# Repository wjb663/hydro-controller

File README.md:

# 26-Computer-Vision-based-hydroponic-control-system

Navigate to "features" branch to get the latest version of the files capable of being ran.

ModusToolbox installation link: https://www.infineon.com/cms/en/design-support/tools/sdk/modustoolbox-software/

Select CY8CPROTO-062-4343W when the IDE has loaded and it will download the relevant drivers. Download WiFi-MQTT_Client_Code example program and replace the code in the files with the code from the features branch. Then run the program and it'll flash to the board.

For the camera:
Two ESP-32s are needed to run the current version of the working code - one for the camera capture, one for the sensor code. The hardware files in our Google drive contain the KICAD files for the camera PCB. There are two version of the camera board - one using an ESP-32 breakout board, the second using a soldered on ESP 32. Both PCB designs contain the pinouts for how the DHT11 sensor, the ambient light sensor, and the Arducam should be connected to each camera board/ESP 32. Connect the DHT11 and ambient light sensor to one ESP32, the ArduCAM to the second.

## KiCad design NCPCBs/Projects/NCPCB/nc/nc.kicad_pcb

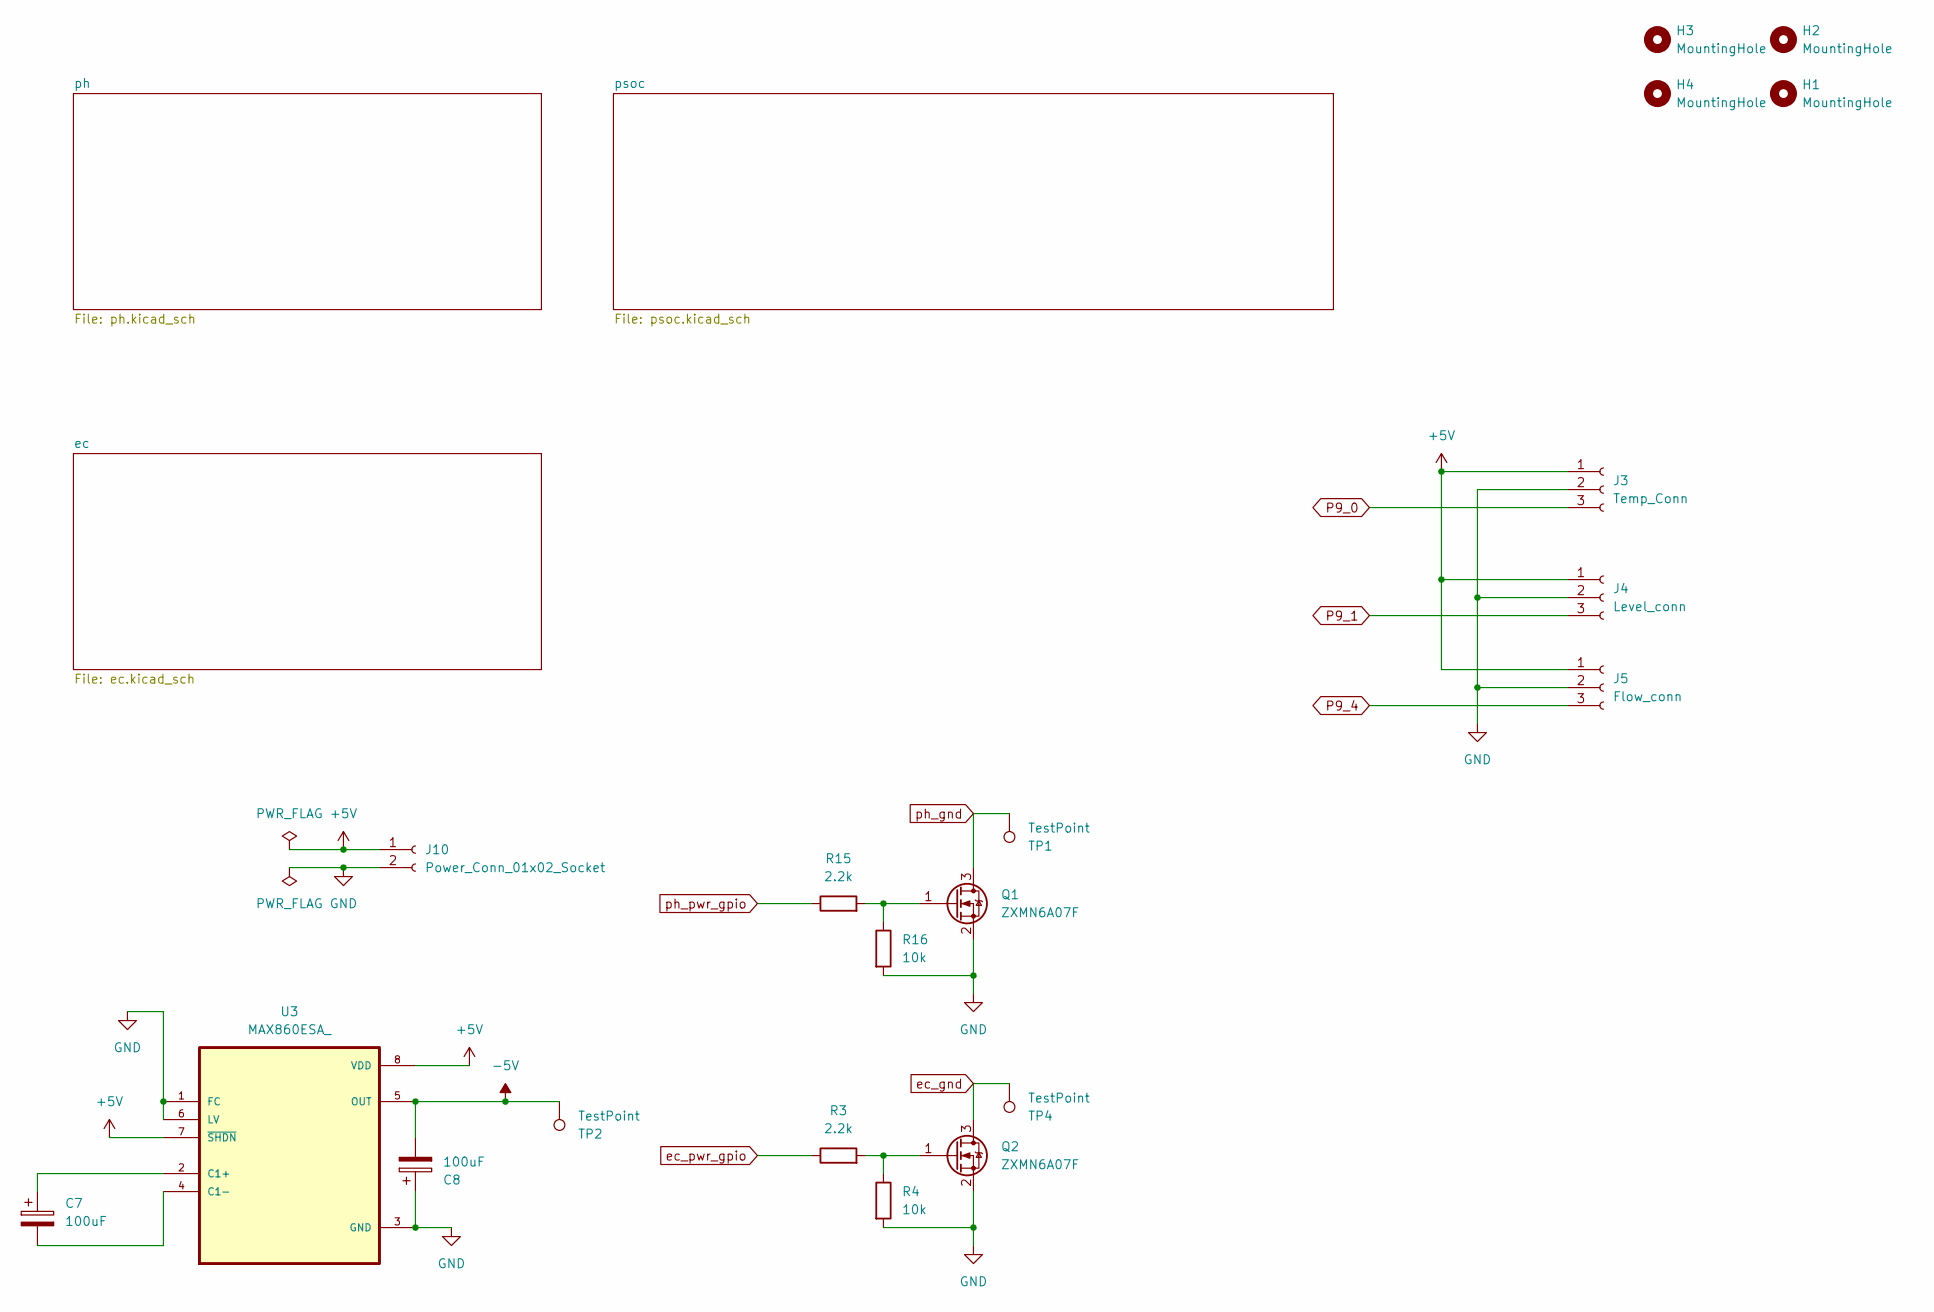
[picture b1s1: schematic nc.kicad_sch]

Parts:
C7, C8: 100uF; CP_EIA-3216-10_Kemet-I_Pad1.58x1.35mm_HandSolder
H1, H2, H3, H4: MountingHole; MountingHole_3.2mm_M3
J3: Temp_Conn; JST_EH_B3B-EH-A_1x03_P2.50mm_Vertical
J4: Level_conn; JST_EH_B3B-EH-A_1x03_P2.50mm_Vertical
J5: Flow_conn; JST_EH_B3B-EH-A_1x03_P2.50mm_Vertical
J10: Power_Conn_01x02_Socket; JST_PH_B2B-PH-K_1x02_P2.00mm_Vertical
Q1, Q2: ZXMN6A07F; SOT-23
R3, R15: 2.2k; R_0805_2012Metric_Pad1.20x1.40mm_HandSolder
R4, R16: 10k; R_0805_2012Metric_Pad1.20x1.40mm_HandSolder
TP1, TP2, TP4: TestPoint; TestPoint_Pad_1.0x1.0mm
U3: MAX860ESA_; SOIC127P600X175-8N

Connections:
+5V: J3.1, J4.1, J5.1, J10.1, U3.7 (~SHDN), U3.8 (VDD); also elsewhere on the board
-5V: C8.2, TP2.1, U3.5 (OUT); also elsewhere on the board
GND: C8.1, J3.2, J4.2, J5.2, J10.2, Q1.2 (S), Q2.2 (S), R4.2, R16.2, U3.1 (FC), U3.3 (GND), U3.6 (LV); also elsewhere on the board
unnamed: Q1.1 (G), R15.2, R16.1
unnamed: Q2.1 (G), R3.2, R4.1
unnamed: C7.1, U3.2 (C1+)
unnamed: C7.2, U3.4 (C1-)
P9_0: J3.3; also elsewhere on the board
P9_1: J4.3; also elsewhere on the board
P9_4: J5.3; also elsewhere on the board
P11_4: R15.1; also elsewhere on the board
P12_3: R3.1; also elsewhere on the board
ec_gnd: Q2.3 (D), TP4.1; also elsewhere on the board
ph_gnd: Q1.3 (D), TP1.1; also elsewhere on the board

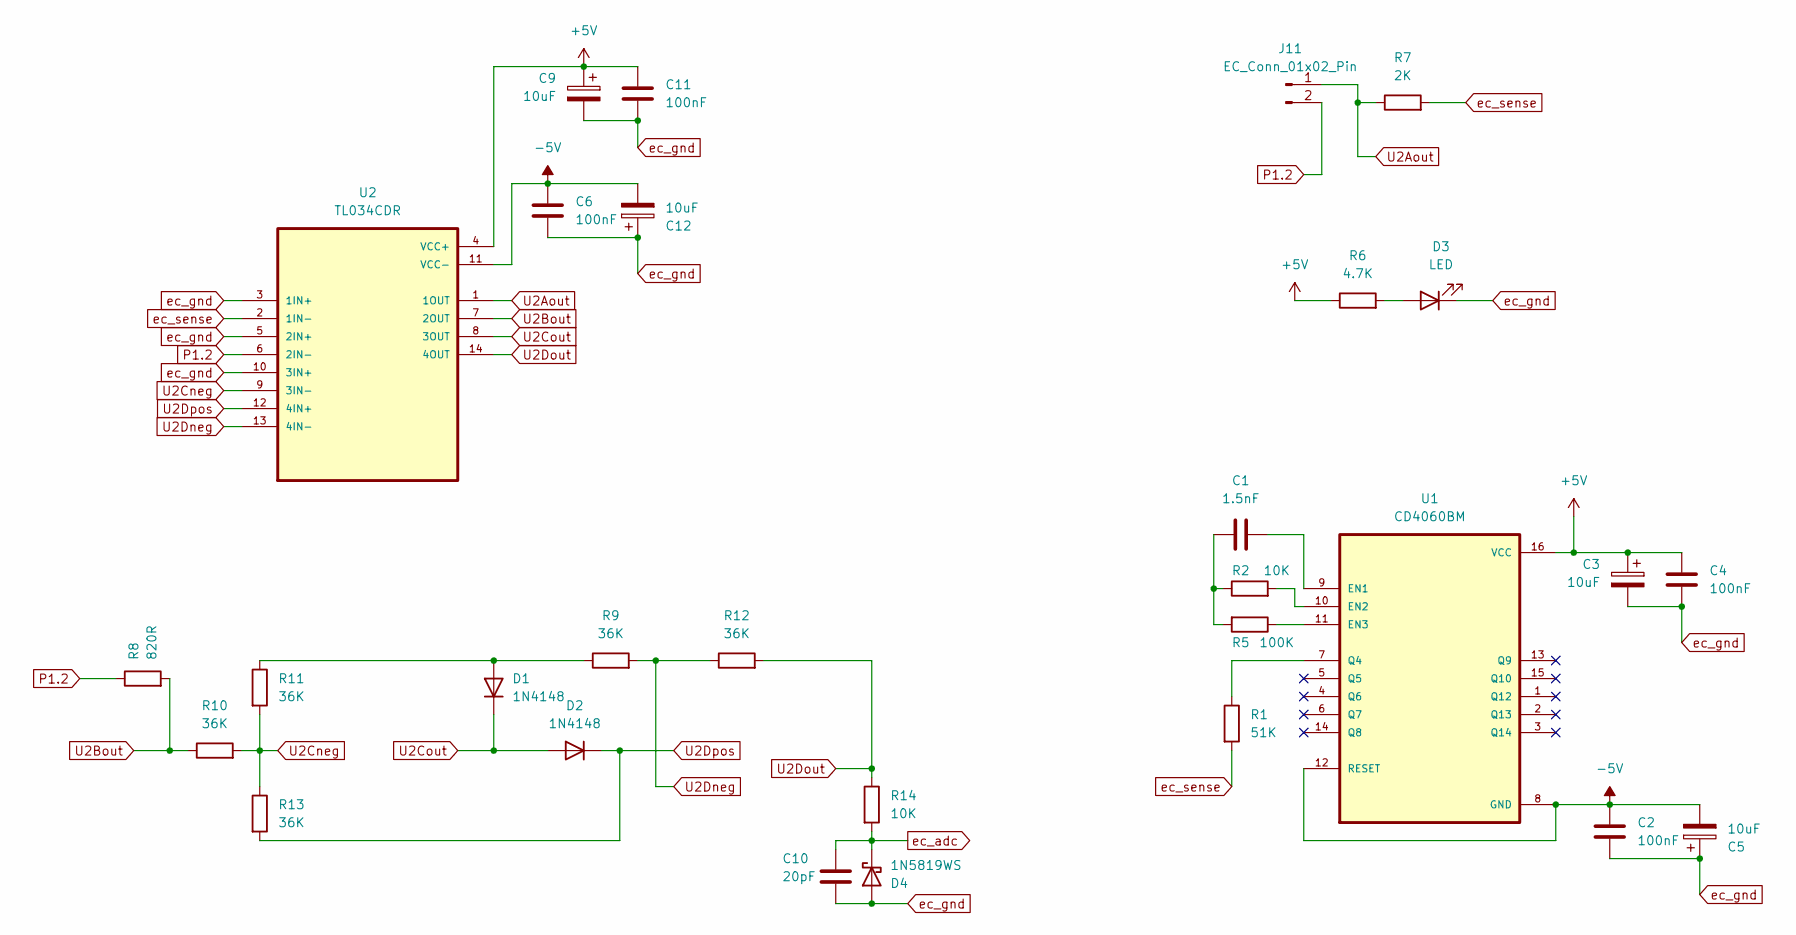
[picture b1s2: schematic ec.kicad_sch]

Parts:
C1: 1.5nF; C_0805_2012Metric_Pad1.18x1.45mm_HandSolder
C2, C4, C6, C11: 100nF; C_0805_2012Metric_Pad1.18x1.45mm_HandSolder
C3, C5, C9, C12: 10uF; CP_EIA-3216-10_Kemet-I_Pad1.58x1.35mm_HandSolder
C10: 20pF; C_0805_2012Metric_Pad1.18x1.45mm_HandSolder
D1, D2: 1N4148; D_DO-35_SOD27_P7.62mm_Horizontal
D3: LED; LED_0805_2012Metric_Pad1.15x1.40mm_HandSolder
D4: 1N5819WS; D_SOD-323
J11: EC_Conn_01x02_Pin; JST_EH_B2B-EH-A_1x02_P2.50mm_Vertical
R1: 51K; R_0805_2012Metric_Pad1.20x1.40mm_HandSolder
R2, R14: 10K; R_0805_2012Metric_Pad1.20x1.40mm_HandSolder
R5: 100K; R_0805_2012Metric_Pad1.20x1.40mm_HandSolder
R6: 4.7K; R_0805_2012Metric_Pad1.20x1.40mm_HandSolder
R7: 2K; R_0805_2012Metric_Pad1.20x1.40mm_HandSolder
R8: 820R; R_0805_2012Metric_Pad1.20x1.40mm_HandSolder
R9, R10, R11, R12, R13: 36K; R_0805_2012Metric_Pad1.20x1.40mm_HandSolder
U1: CD4060BM; SOIC127P600X175-16N
U2: TL034CDR; SOIC127P600X175-14N

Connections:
+5V: C3.1, C4.1, C9.1, C11.1, R6.1, U1.16 (VCC), U2.4 (VCC+); also elsewhere on the board
-5V: C2.1, C5.2, C6.1, C12.2, U1.8 (GND), U1.12 (RESET), U2.11 (VCC-); also elsewhere on the board
unnamed: C1.1, R2.1, R5.2
unnamed: D1.2 (A), R9.1, R11.1
unnamed: D3.2 (A), R6.2
unnamed: C1.2, U1.9 (EN1)
unnamed: R2.2, U1.10 (EN2)
unnamed: R5.1, U1.11 (EN3)
unnamed: R1.1, U1.7 (Q4)
P1.2: J11.2, R8.1, U2.6 (2IN-)
P10_3: C10.1, D4.1 (K), R14.2; also elsewhere on the board
U2Aout: J11.1, R7.1, U2.1 (1OUT)
U2Bout: R8.2, R10.1, U2.7 (2OUT)
U2Cneg: R10.2, R11.2, R13.1, U2.9 (3IN-)
U2Cout: D1.1 (K), D2.2 (A), U2.8 (3OUT)
U2Dneg: R9.2, R12.1, U2.13 (4IN-)
U2Dout: R12.2, R14.1, U2.14 (4OUT)
U2Dpos: D2.1 (K), R13.2, U2.12 (4IN+)
ec_gnd: C2.2, C3.2, C4.2, C5.1, C6.2, C9.2, C10.2, C11.2, C12.1, D3.1 (K), D4.2 (A), U2.3 (1IN+), U2.5 (2IN+), U2.10 (3IN+); also elsewhere on the board
ec_sense: R1.2, R7.2, U2.2 (1IN-)

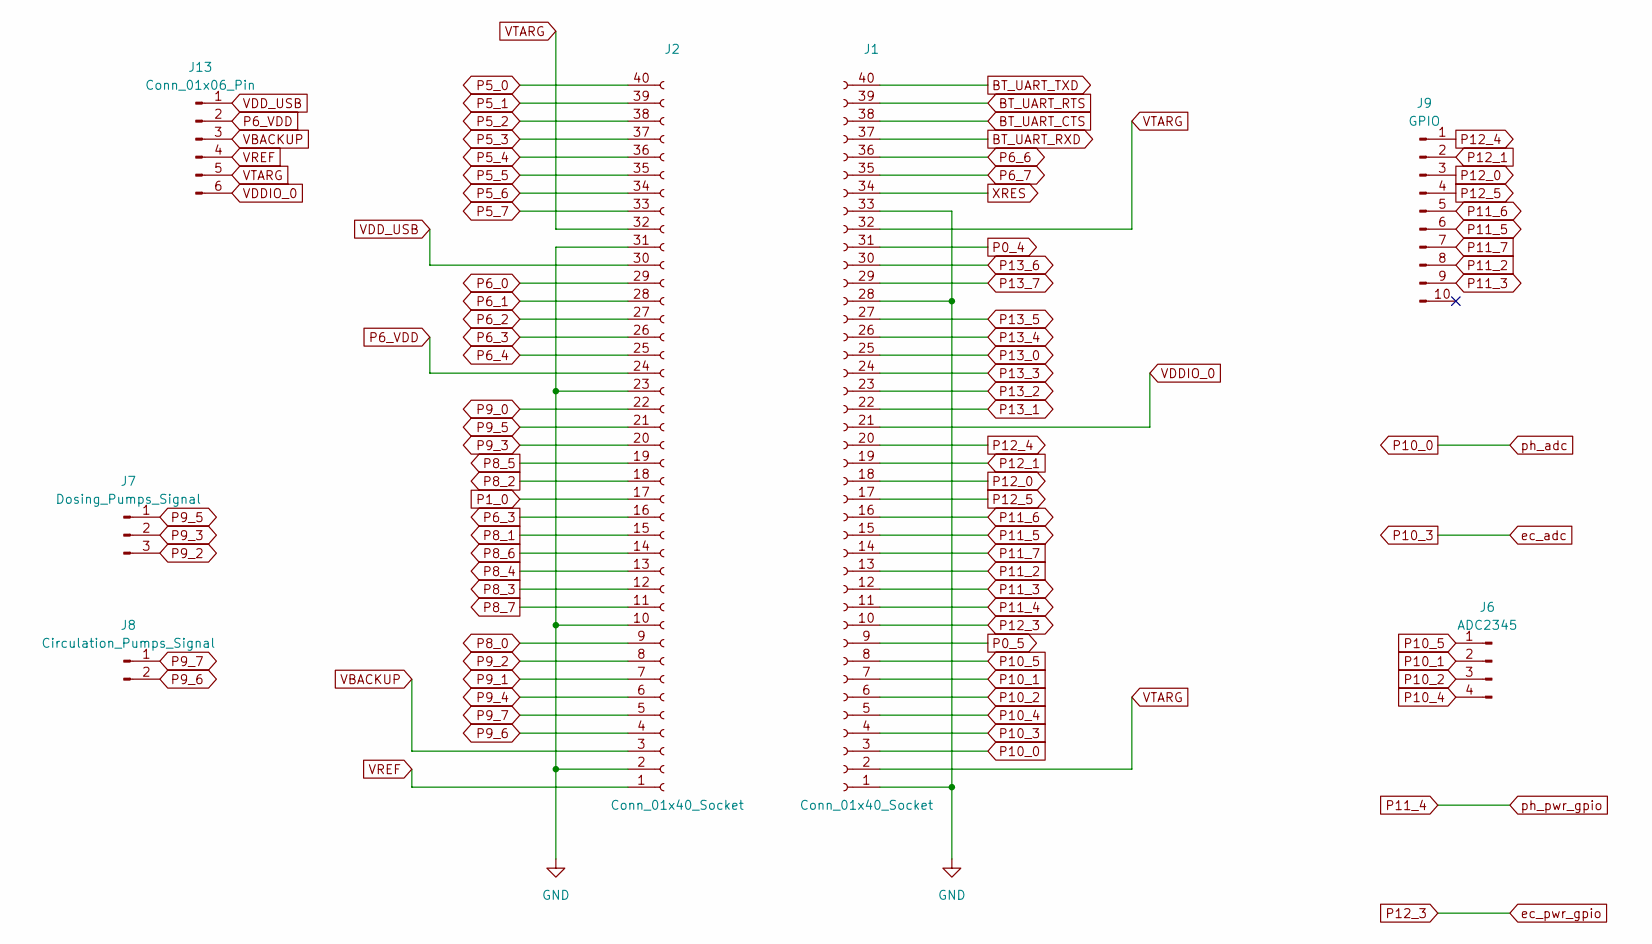
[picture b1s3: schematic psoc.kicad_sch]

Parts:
J1, J2: Conn_01x40_Socket; PinSocket_1x40_P2.00mm_Vertical
J6: ADC2345; PinHeader_1x04_P2.00mm_Vertical
J7: Dosing_Pumps_Signal; JST_EH_B3B-EH-A_1x03_P2.50mm_Vertical
J8: Circulation_Pumps_Signal; JST_EH_B2B-EH-A_1x02_P2.50mm_Vertical
J9: GPIO; PinHeader_1x10_P2.00mm_Vertical
J13: Conn_01x06_Pin; PinHeader_1x06_P2.00mm_Vertical

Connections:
BT_UART_CTS: J1.38
BT_UART_RTS: J1.39
BT_UART_RXD: J1.37
BT_UART_TXD: J1.40
GND: J1.1, J1.28, J1.33, J2.2, J2.10, J2.23, J2.31; also elsewhere on the board
P0_4: J1.31
P0_5: J1.9
P1_0: J2.17
P5_0: J2.40
P5_1: J2.39
P5_2: J2.38
P5_3: J2.37
P5_4: J2.36
P5_5: J2.35
P5_6: J2.34
P5_7: J2.33
P6_0: J2.29
P6_1: J2.28
P6_2: J2.27
P6_3: J2.16, J2.26
P6_4: J2.25
P6_6: J1.36
P6_7: J1.35
P6_VDD: J2.24, J13.2
P8_0: J2.9
P8_1: J2.15
P8_2: J2.18
P8_3: J2.12
P8_4: J2.13
P8_5: J2.19
P8_6: J2.14
P8_7: J2.11
P9_0: J2.22; also elsewhere on the board
P9_1: J2.7; also elsewhere on the board
P9_2: J2.8, J7.3
P9_3: J2.20, J7.2
P9_4: J2.6; also elsewhere on the board
P9_5: J2.21, J7.1
P9_6: J2.4, J8.2
P9_7: J2.5, J8.1
P10_0: J1.3; also elsewhere on the board
P10_1: J1.7, J6.2
P10_2: J1.6, J6.3
P10_3: J1.4; also elsewhere on the board
P10_4: J1.5, J6.4
P10_5: J1.8, J6.1
P11_2: J1.13, J9.8
P11_3: J1.12, J9.9
P11_4: J1.11; also elsewhere on the board
P11_5: J1.15, J9.6
P11_6: J1.16, J9.5
P11_7: J1.14, J9.7
P12_0: J1.18, J9.3
P12_1: J1.19, J9.2
P12_3: J1.10; also elsewhere on the board
P12_4: J1.20, J9.1
P12_5: J1.17, J9.4
P13_0: J1.25
P13_1: J1.22
P13_2: J1.23
P13_3: J1.24
P13_4: J1.26
P13_5: J1.27
P13_6: J1.30
P13_7: J1.29
VBACKUP: J2.3, J13.3
VDDIO_0: J1.21, J13.6
VDD_USB: J2.30, J13.1
VREF: J2.1, J13.4
VTARG: J1.2, J1.32, J2.32, J13.5
XRES: J1.34

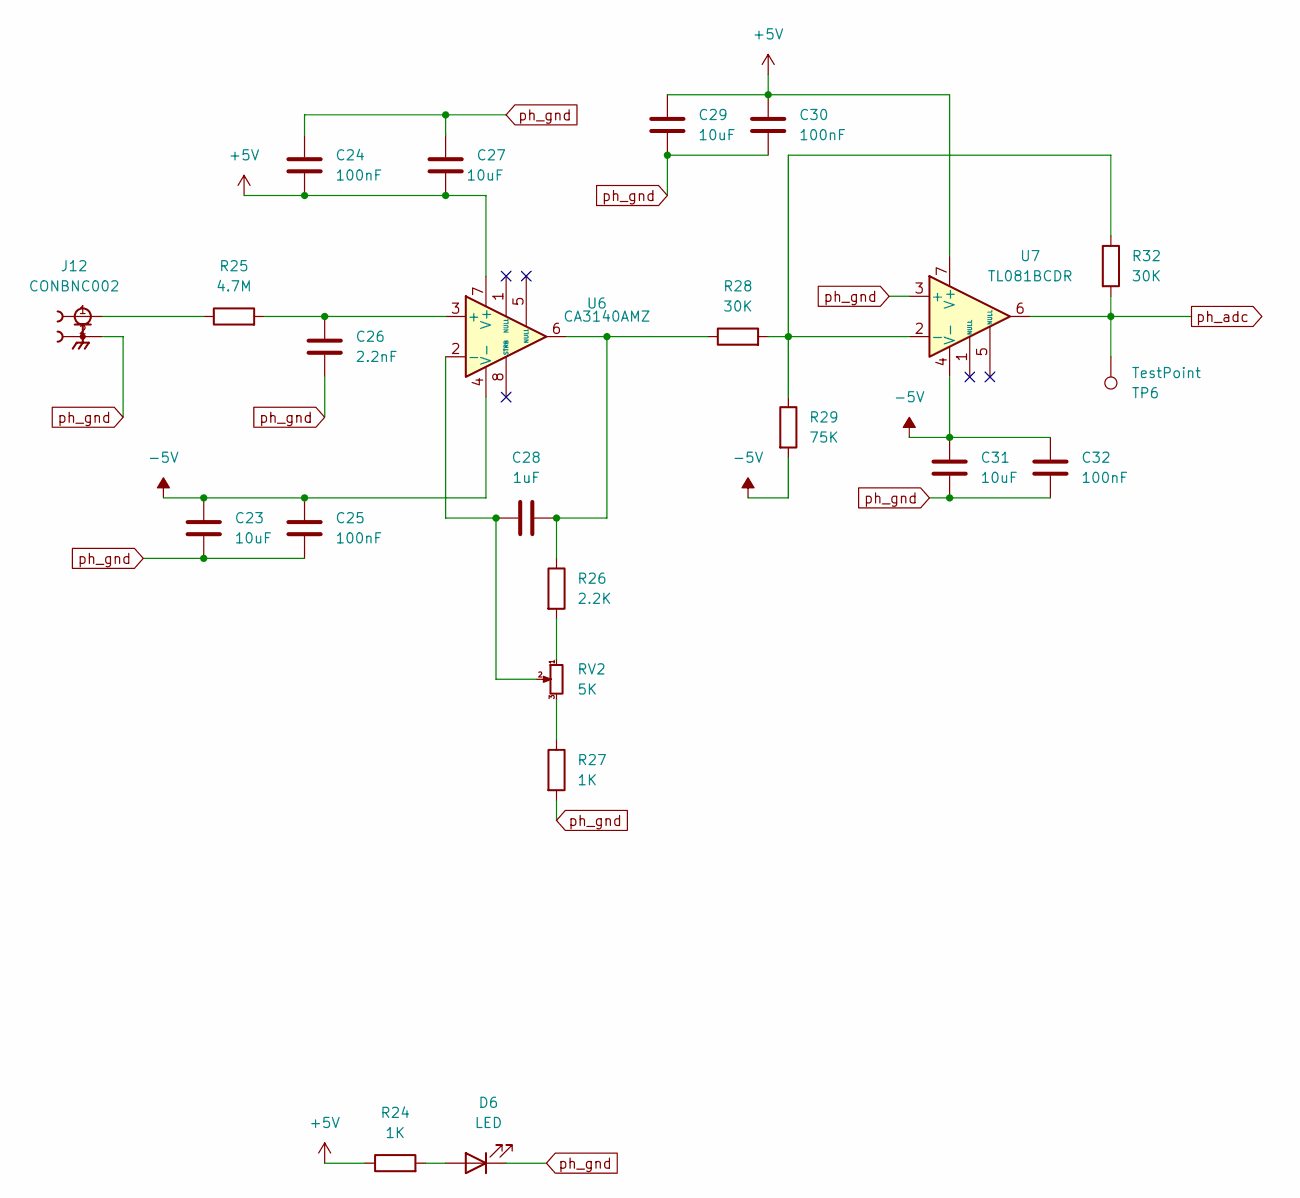
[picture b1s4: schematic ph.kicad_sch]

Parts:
C23, C27, C29, C31: 10uF; C_0805_2012Metric_Pad1.18x1.45mm_HandSolder
C24, C25, C30, C32: 100nF; C_0805_2012Metric_Pad1.18x1.45mm_HandSolder
C26: 2.2nF; C_0805_2012Metric_Pad1.18x1.45mm_HandSolder
C28: 1uF; C_0805_2012Metric_Pad1.18x1.45mm_HandSolder
D6: LED; LED_0805_2012Metric_Pad1.15x1.40mm_HandSolder
J12: CONBNC002; LINX_CONBNC002
R24, R27: 1K; R_0805_2012Metric_Pad1.20x1.40mm_HandSolder
R25: 4.7M; R_0805_2012Metric_Pad1.20x1.40mm_HandSolder
R26: 2.2K; R_0805_2012Metric_Pad1.20x1.40mm_HandSolder
R28, R32: 30K; R_0805_2012Metric_Pad1.20x1.40mm_HandSolder
R29: 75K; R_0805_2012Metric_Pad1.20x1.40mm_HandSolder
RV2: 5K; Potentiometer_Bourns_3266W_Vertical
TP6: TestPoint; TestPoint_Pad_1.0x1.0mm
U6: CA3140AMZ; SOIC-8_3.9x4.9mm_P1.27mm
U7: TL081BCDR; SOIC-8_3.9x4.9mm_P1.27mm

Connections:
+5V: C24.2, C27.2, C29.1, C30.1, R24.1, U6.7 (V+), U7.7 (V+); also elsewhere on the board
-5V: C23.1, C25.1, C31.1, C32.1, R29.2, U6.4 (V-), U7.4 (V-); also elsewhere on the board
unnamed: C28.2, R26.1, R28.1, U6.6
unnamed: D6.2 (A), R24.2
unnamed: J12.1, R25.1
unnamed: R26.2, RV2.1
unnamed: R27.1, RV2.3
unnamed: C26.1, R25.2, U6.3 (+)
unnamed: C28.1, RV2.2, U6.2 (-)
unnamed: R28.2, R29.1, R32.1, U7.2 (-)
P10_0: R32.2, TP6.1, U7.6; also elsewhere on the board
ph_gnd: C23.2, C24.1, C25.2, C26.2, C27.1, C29.2, C30.2, C31.2, C32.2, D6.1 (K), J12.2, R27.2, U7.3 (+); also elsewhere on the board

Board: 2 copper layers, 79 parts (0 on the bottom side), 65 nets, no tracks yet.

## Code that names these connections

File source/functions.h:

#include "cybsp.h"
#include "cyhal.h"


#ifndef SOURCE_SENSOR_FUNCTIONS_H_
#define SOURCE_SENSOR_FUNCTIONS_H_

#define VPLUS_CHANNEL_0  (P10_0)
#define VPLUS_CHANNEL_1  (P10_3)
#define VREF_CHANNEL_1   (P10_5)

/* Number of scans every time ADC read is initiated */
#define NUM_SCAN                    (1)

/* Conversion factor */
#define MICRO_TO_MILLI_CONV_RATIO        (1000u)

/* Acquistion time in nanosecond */
#define ACQUISITION_TIME_NS              (1000u)

/* ADC Scan delay in millisecond */
#define ADC_SCAN_DELAY_MS                (200u)
#define NUM_READINGS					 (10)

/* Number of scans every time ADC read is initiated */
#define NUM_SCAN                         (1)

//Pin Macros
#define PH_FET                          (P11_4)
#define EC_FET                          (P12_3)

#define PUMP_ONE                        (P9_5)
#define PUMP_TWO                        (P9_3)
#define PUMP_THREE                      (P9_2)
#define PUMP_FOUR                       (P9_7)
#define PUMP_FIVE                       (P9_6)

void gpio_init();

void adc_multi_channel_init(void);
cy_rslt_t result_return(void);
int32_t channel0_return(void);
int32_t channel1_return(void);

#endif /* SOURCE_SENSOR_FUNCTIONS_H_ */

/*******************************************************************************
* Function Prototypes
*******************************************************************************/
void timer_init(void);


/* Single channel initialization function*/
void adc_single_channel_init(void);

/* Function to read input voltage from channel 0 */
void adc_single_channel_process(void);

//Temp Sensor Functions
void initialize_wire(void);
void wire_process(void *pvParameters);
void write_wire_byte(uint8_t data);
void read_wire(void);
void print_wire(void);

//Pumps
// void pump_task(void *pvParameters);

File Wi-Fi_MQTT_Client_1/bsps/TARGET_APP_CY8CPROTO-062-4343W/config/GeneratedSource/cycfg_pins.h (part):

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    #define CYBSP_USER_BTN1 CYBSP_SW2
    #define CYBSP_USER_BTN CYBSP_SW2
    #define CYBSP_WIFI_HOST_WAKE CYBSP_SW2
    #define CYBSP_PDM_CLK (P10_4)
    #define CYBSP_PDM_DATA (P10_5)
    #define CYBSP_QSPI_SS (P11_2)
    #define CYBSP_QSPI_D3 (P11_3)
    #define CYBSP_QSPI_D2 (P11_4)
    #define CYBSP_QSPI_D1 (P11_5)
    #define CYBSP_QSPI_D0 (P11_6)
    #define CYBSP_QSPI_SCK (P11_7)
    #define CYBSP_SDHC_CMD (P12_4)
    #define CYBSP_SDHC_CLK (P12_5)
    #define CYBSP_SDHC_IO0 (P13_0)
    #define CYBSP_SDHC_IO1 (P13_1)
    #define CYBSP_SDHC_IO2 (P13_2)
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
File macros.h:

//Macros for program
#include "cyhal.h"


typedef enum transaction{
    RESET,
    PRESENSE,
    SKIP_ROM,
    CONVERT_T,
    POLL,
    SCRATCH,
    PARSE,
    DONE,
    ERROR,
} transaction_t;



/*******************************************************************************
* Macros
*******************************************************************************/
/* LED blink timer clock value in Hz  */
#define LED_BLINK_TIMER_CLOCK_HZ          (10000)

/* LED blink timer period value */
#define LED_BLINK_TIMER_PERIOD            (9999)

#define PUMP_TIMER_CLOCK_HZ               (10000)
#define PUMP_TIMER_PERIOD                 (9999)

#define WIRE_TIMER_CLOCK_HZ               (100000)
#define WIRE_TIMER_PERIOD                 (50)

#define WRITE_TIMER_CLOCK_HZ               (1000000)
#define WRITE_TIMER_PERIOD                 (100)  

#define READ_TIMER_CLOCK_HZ               (1000000)
#define READ_TIMER_PERIOD                 (10) 

#define WRITE_TIMER_SLOT                 (12)     

#define INIT_RETRIES                    (10)
#define REG_SIZE                        (16)


#define FLOW_PIN                        P9_1
#define TEMP_PIN                        P9_0

#define CIRC_PUMP_IN

#define DOSE_PUMP_A                     P9_2

#define PHFET                           P11_4
#define TDSFET                          P12_3
#define PH_CHANNEL                       P10_0
#define EC_CHANNEL                       P10_3

/* Conversion factor */
#define MICRO_TO_MILLI_CONV_RATIO        (1000u)

/* Acquistion time in nanosecond */
#define ACQUISITION_TIME_NS              (1000u)

/* ADC Scan delay in millisecond */
#define ADC_SCAN_DELAY_MS                (200u)

#define RING_BUFFER_SIZE                (16)

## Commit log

2023-11-09 Update README.md
    Added README requirements headings.
2023-11-09 Create Tasks
    Roadmap/Process for constructing the embedded code.
2024-01-17 Uploading MQTT WiFi files and MTB_shared
2024-01-18 Revert "Uploading MQTT WiFi files and MTB_shared"
    This reverts commit b8bda4247cb60f49cb98cf42f1170a6004a43c0a.
2024-01-18 Example_Program_Code
    Uploading mtb_shared and wifi_mqtt code from tech demo
2024-01-18 Revert "Example_Program_Code"
    This reverts commit f171c7ba359dec11759c3ba099fc9b582c5109f9.
2024-01-18 Wi-Fi code
2024-01-18 mtb_shared files
2024-01-18 Revert "mtb_shared files"
    This reverts commit e1da13763e985f4f9b1cb21dc1ca3114a65bc013.
2024-01-18 removed wifi code
2024-01-18 wifi files
2024-01-21 Added test file.
2024-01-21 Updated Test File
2024-02-06 Implemented multiple git project folder structure and PCBs
    -Added top level folders for NutrientController, Camera, and NCPCBS.
    -Added NCPCB project files
2024-03-31 Deleted outdated folder.
2024-03-31 Deleted old files and copied project folder.
2024-03-31 Created Workspace file.
2024-03-31 Created 1-Wire timer. Declared Temp sensor functions.
2024-03-31 Started initilization code. Made ringBuffer volatile. Callback GPIOs.
2024-03-31 Created finction prototype file. Refactored function locations.
2024-04-01 Timers for 1-wire initialization and read/write slots.
2024-04-01 Redefined transaction enum.
2024-04-02 Create git.
2024-04-02 Deleted old project.
2024-04-02 Changed channel 1 to single ended mode. Changed channel 1 pin macro.
2024-04-02 Added pin macros .
2024-04-02 Removed default sample messages.
2024-04-02 Moved pin macros to functions header file. Updated gpio init function with pin macros.
2024-04-03 Changed 1-wire initialization process.
2024-04-03 Completed 1-Wire initialization.
2024-04-04 Added writing to 1-wire functionality.
2024-04-04 Added 1-wire read timer.
2024-04-04 Added read 1-wire functionality. Completed state machine for temperature aquisition.
2024-04-05 Changed settings to accomodate multiple users.
2024-04-05 Merged functions header files.
2024-04-05 Merged gpio initialization.
2024-04-05 Merged timers and ISRs.
2024-04-05 Refactor.
2024-04-13 Moved init functions to main. Created Temperature RTOS task.
2024-04-14 Added temperature reset to publisher task.
2024-04-14 Changed temperature transaction update away from timer ISRs.
2024-04-14 Changed read timer.
2024-04-16 Commented out VSCode files from .gitignore.
2024-04-16 UnCommented VSCode files from .gitignore.
2024-04-16 Added Pump Sub Topics.
2024-04-17 Changed subscriber_data_t to accept char cmd.
2024-04-17 Added dose pump timer/counter code. Completed dose pump subscriber topics.
2024-04-17 Changed pH reading output to pH instead of voltage. Added temperature publishing. Added circulation and empty pump topics.

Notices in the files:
Wi-Fi_MQTT_Client_1/bsps/TARGET_APP_CY8CPROTO-062-4343W/config/GeneratedSource/cycfg_pins.h:
Copyright 2023 Cypress Semiconductor Corporation (an Infineon company) or
an affiliate of Cypress Semiconductor Corporation.
SPDX-License-Identifier: Apache-2.0
Licensed under the Apache License, Version 2.0 (the "License");
